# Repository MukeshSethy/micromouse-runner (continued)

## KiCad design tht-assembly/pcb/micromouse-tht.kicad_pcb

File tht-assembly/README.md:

# THT Assembly — the self-solderable micromouse carrier board (KiCad project)

This folder is the **executable KiCad project** for the all-THT edition
chartered in [`../tht-variant/`](../tht-variant/) (BOM research, architecture
decisions, ordering flow live there — read it first).

**Everything here is script-generated**, same discipline as the SMD board:

```
tht-assembly/
├── pcb/
│   ├── micromouse-tht.kicad_sch / .kicad_pcb   generated outputs
│   ├── netlist.net                             schematic's own export
│   ├── n20.pretty/                             optic footprints (shared)
│   └── tools/
│       ├── build_schematic_tht.py   FULL schematic (198 syms, ERC 0,
│       │                            RAIL-only — no wire doglegs possible)
│       ├── build_pcb_tht.py         outline + placement (measured-courtyard
│       │                            greedy packers; 0 overlaps) + planes
│       ├── route_tht.py             A* routing (power 0.8mm, signals 0.4mm)
│       └── verify_drc.py …          the SMD project's gate suite, path-adapted
└── images/                          renders
```

## Key physical decisions (why the board looks like this)
- **Sensor geometry copied verbatim** from the rev-7.2 SMD board (D1-D6,
  Q2-Q7 wall optics at 0°/45°/90°, LS1-LS8 line array) — it is the
  research-verified core of the robot and all three families were already THT.
- **DevKitC-1 lies across the rear** on two 1×22 sockets (rows y94.5/117.36,
  USB end to the right, kept clear). The SMD board's antenna notch is gone —
  the DevKit's antenna rides ~10 mm above the board.
- **The mux DIP is soldered flat under the DevKit deck** (no socket — 4.3 mm
  under an 8.5 mm deck). Everything else under the deck is bare board.
- **Bottom face carries the silent majority**: all 66 axial resistors,
  20 TO-92 transistors, the flyback diode and the piezo — all under the
  ~7 mm ride-height budget. Top face keeps everything you look at or touch:
  optics, LEDs, buttons, connectors, power bricks, sockets.
- **Motor bays own the waist** (x2.7-46.2 / x53.8-97.3, y76.9-91.1 top): the
  only top-face items there are the wall-LED row and motor connectors at its
  forward edge.

## Assembly / bring-up
Follow [`../tht-variant/ORDERING.md`](../tht-variant/ORDERING.md) (bare-PCB
fab + parts kit + three robu modules). Solder bottom-face resistors first
(board flat), then work upward by height. Firmware: the shared `fw/` tree —
GPIO numbers are IDENTICAL to the SMD board (same S3 silicon); flash through
the DevKit's own USB-C.

## Placement (pre-routing, for review)

> These are PLACEMENT renders (no traces yet) — routing + DRC follow. Wall
> sensors sit on the perimeter facing outward with clear IR paths; indicators
> are inboard behind them; all support parts + both RGB drivers + the buzzer
> are on the bottom face.

**Top** — sensors (perimeter), indicators (inboard), power block, DevKit +
TB6612 sockets, buttons, RGB LEDs:

**Bottom** — axial resistors, TO-92 transistors, buzzer, flyback diode:

## Status
See the milestone log in git (`THT assembly M1..`): schematic ERC 0 →
placement 0-overlap + optical-clear → routing → DRC gate → fab package.
**Current: placement complete & optically verified; routing in progress.**

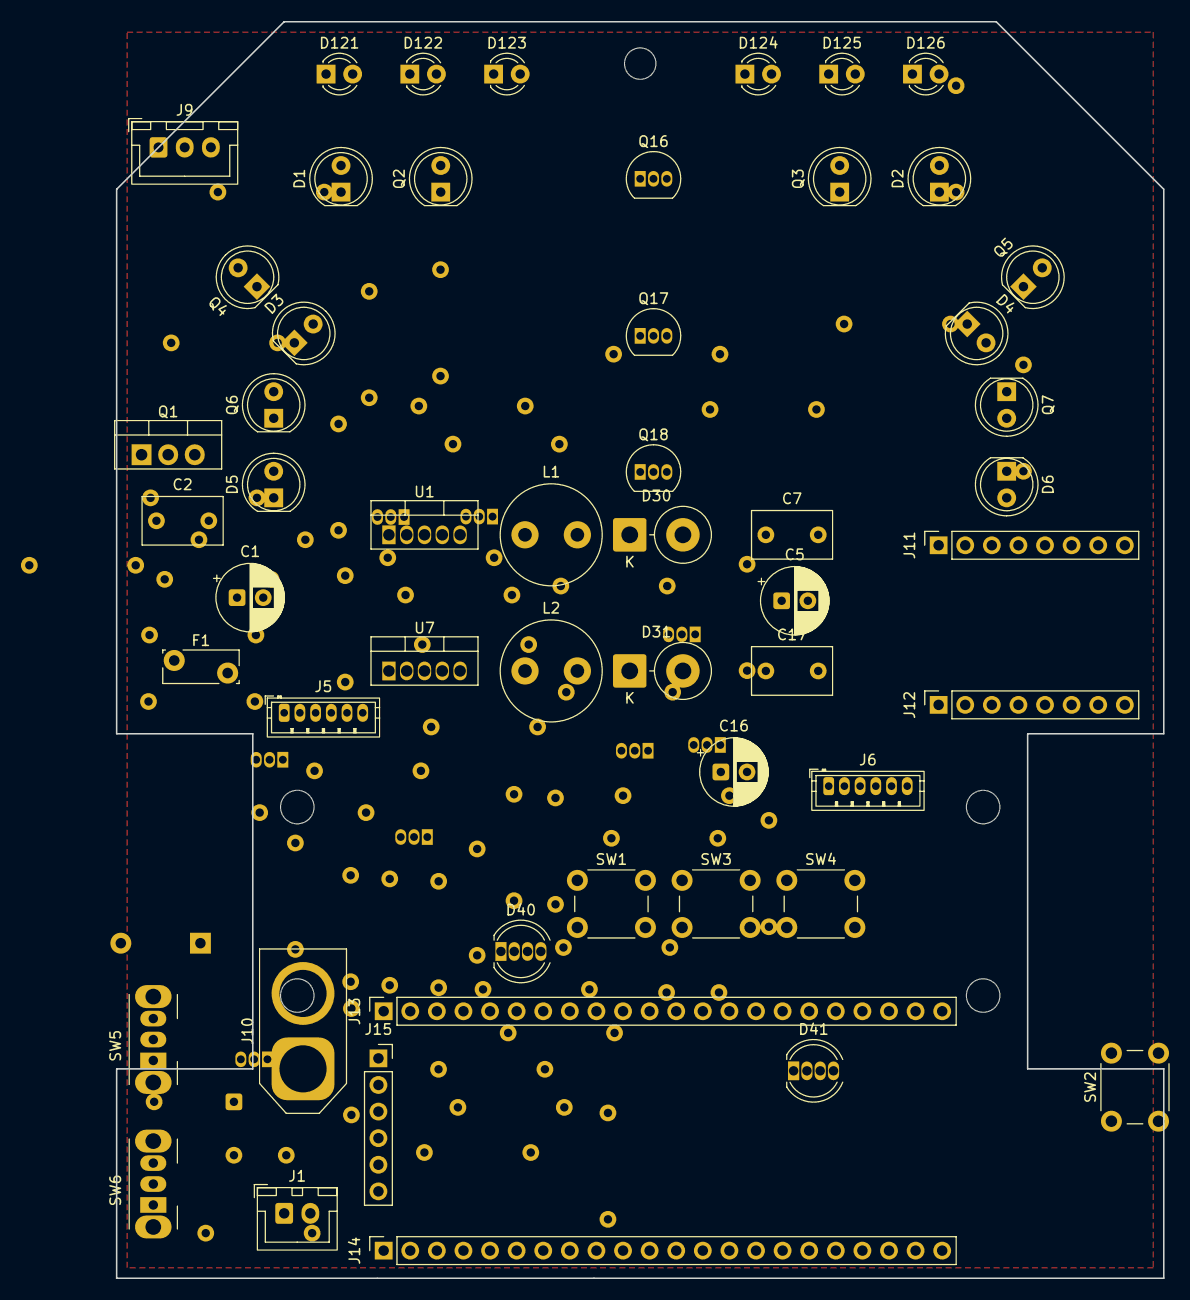
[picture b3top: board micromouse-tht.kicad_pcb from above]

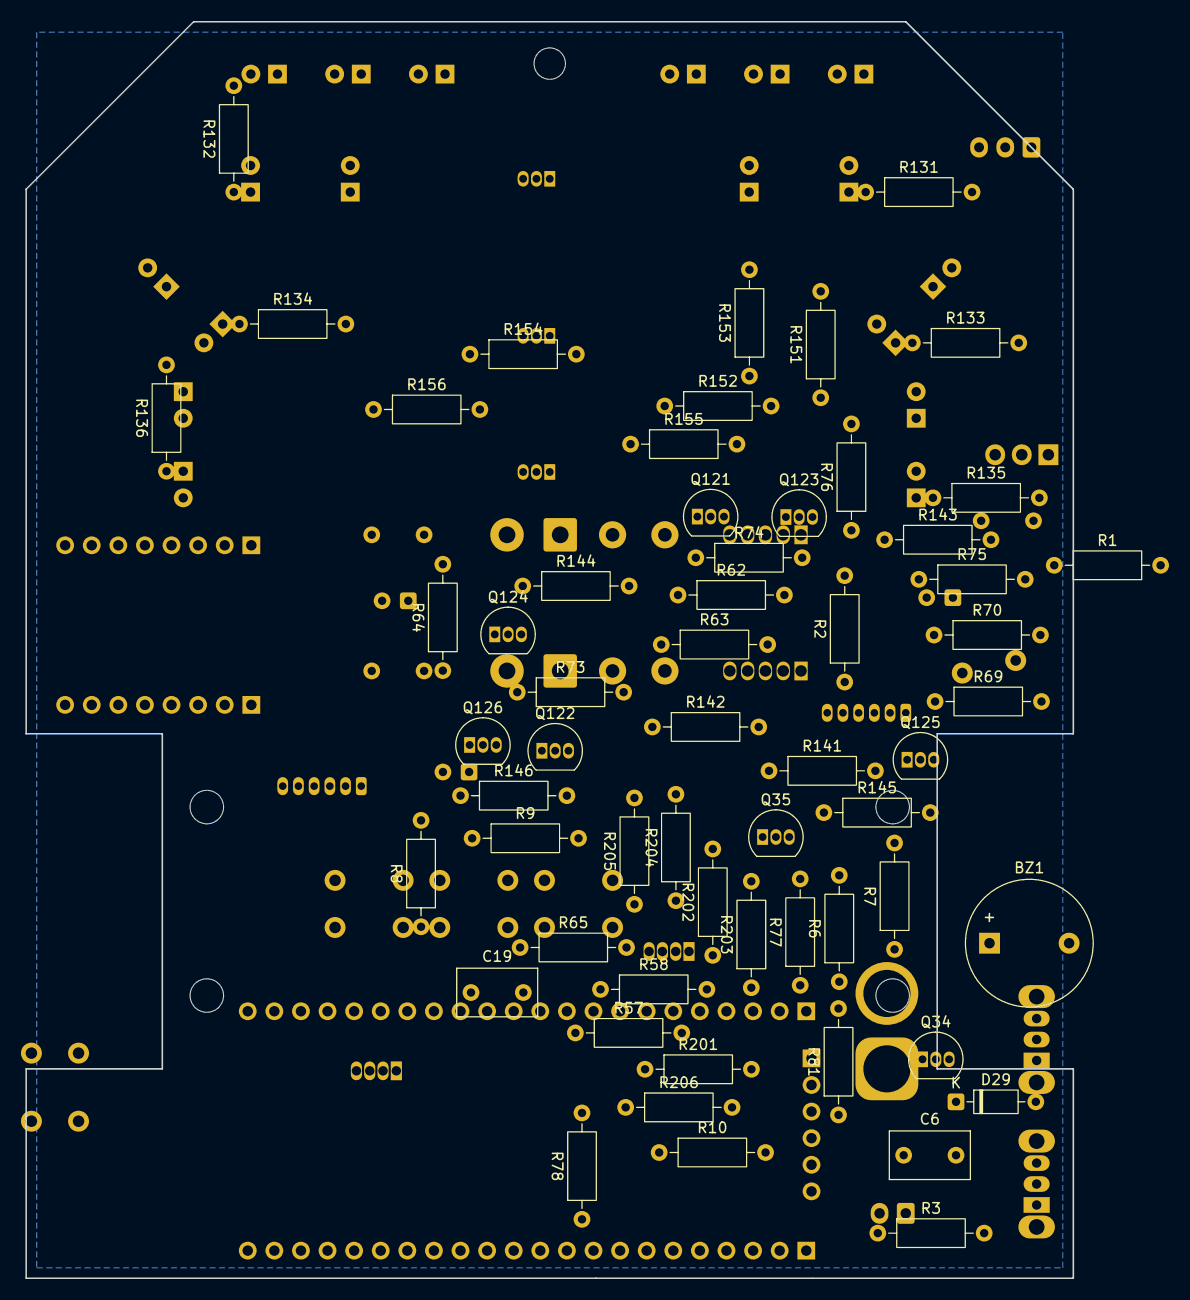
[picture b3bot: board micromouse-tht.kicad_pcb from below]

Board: 2 copper layers, 100.0 x 120.0 mm, 117 parts (59 on the bottom side), 82 nets, no tracks yet.

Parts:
BZ1: Buzzer_12x9.5RM7.6
C1, C5, C16: CP_Radial_D6.3mm_P2.50mm
C2, C6, C7, C17, C19: C_Disc_D7.5mm_W4.4mm_P5.00mm
D1, D2, D3, D4, D5, D6: LED_D5.0mm_IRGrey
D29: D_DO-35_SOD27_P7.62mm_Horizontal
D30, D31: D_DO-201AD_P5.08mm_Vertical_CathodeUp
D40, D41: LED_D5.0mm-4_RGB
D121, D122, D123, D124, D125, D126: LED_D3.0mm
F1: Fuse_Bourns_MF-RG300
H1, H2, H3, H4, H5: MountingHole_NPTH
J1: JST_XH_B2B-XH-A_1x02_P2.50mm_Vertical
J5, J6: JST_ZH_B6B-ZR_1x06_P1.50mm_Vertical
J9: JST_XH_B3B-XH-A_1x03_P2.50mm_Vertical
J10: AMASS_XT60-M_1x02_P7.20mm_Vertical
J11, J12: PinSocket_1x08_P2.54mm_Vertical
J13, J14: PinSocket_1x22_P2.54mm_Vertical
J15: PinSocket_1x06_P2.54mm_Vertical
L1, L2: L_Radial_D9.5mm_P5.00mm_Fastron_07HVP
Q1: TO-220-3_Vertical
Q2, Q3, Q4, Q5, Q6, Q7: LED_D5.0mm_IRBlack
Q16, Q17, Q18, Q34, Q35, Q121, Q122, Q123, Q124, Q125, Q126: TO-92_Inline
R1, R2, R3, R6, R7, R8, R9, R10, R57, R58, R62, R63, R64, R65, R69, R70, R73, R74, R75, R76, R77, R78, R81, R131, R132, R133, R134, R135, R136, R141, R142, R143, R144, R145, R146, R151, R152, R153, R154, R155, R156, R201, R202, R203, R204, R205, R206: R_Axial_DIN0207_L6.3mm_D2.5mm_P10.16mm_Horizontal
SW1, SW2, SW3, SW4: SW_PUSH_6mm
SW5, SW6: SW_Slide_SPDT_Angled_CK_OS102011MA1Q
U1, U7: TO-220-5_Vertical

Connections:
AIN1: J11.3, J13.15
AIN2: J11.2, J13.16
BATT_RAW: F1.1, J1.1, J9.3, J10.1
BAT_MID: J9.2, R75.1
BAT_MID_SENSE: C19.1, J13.12, R75.2, R76.1
BIN1: J11.5, J14.10
BIN2: J11.6, J14.15, R65.1
BUZZ_B: Q34.2, R81.2
BUZZ_CTRL: J13.14, R81.1
BUZZ_DRV: BZ1.2, D29.2, Q34.3
EMIT_DIAG_K: D3.1, D4.1, Q17.3
EMIT_FRONT_K: D1.1, D2.1, Q16.3
EMIT_SIDE_K: D5.1, D6.1, Q18.3
ENC1_A: J5.3, J14.17, R6.2
ENC1_B: J5.4, J14.16, R7.2
ENC2_A: J6.3, R8.2, R57.1
ENC2_A_S3: J14.3, R57.2
ENC2_B: J6.4, R9.2, R58.1
ENC2_B_S3: J14.2, R58.2
ESP_RST: J13.3, SW2.1
F1_OUT: F1.2, Q1.2
FB_6V: R73.2, R74.1, U7.4
GND: C1.2, C2.2, C5.2, C6.2, C7.2, C16.2, C17.2, C19.2, D30.2, D31.2, D40.2, D41.2, D121.1, D122.1, D123.1, D124.1, D125.1, D126.1, J1.2, J5.5, J6.5, J9.1, J10.2, J11.8, J12.3, J12.8, J13.22, J14.1, J14.21, J14.22, J15.2, Q2.2, Q3.2, Q4.2, Q5.2, Q6.2, Q7.2, Q16.1, Q17.1, Q18.1, Q34.1, R1.2, R3.2, R62.2, R63.2, R64.2, R65.2, R74.2, R76.2, SW1.2, SW2.2, SW3.2, SW4.2, SW5.3, SW6.3, U1.3, U7.3
IMU_INT: J14.11, J15.5
IMU_SCL: J14.18, J15.3, R78.2
IMU_SDA: J13.11, J15.4, R77.2
MOTA_N: J5.6, J12.5
MOTA_P: J5.1, J12.4
MOTB_N: J6.6, J12.6
MOTB_P: J6.1, J12.7
MOT_EN: Q35.3, R70.2, U7.5
MOT_EN_SW: Q35.1, SW6.1, SW6.2
unnamed: D1.2, R131.2
unnamed: D2.2, R132.2
unnamed: D3.2, R133.2
unnamed: D4.2, R134.2
unnamed: D5.2, R135.2
unnamed: D6.2, R136.2
PLUS3V3: BZ1.1, C5.1, C7.1, D29.1, J5.2, J6.2, J11.1, J11.4, J11.7, J12.2, J13.1, J13.2, J15.1, L1.2, Q35.2, Q121.3, Q122.3, Q123.3, Q124.3, Q125.3, Q126.3, R6.1, R7.1, R8.1, R9.1, R10.1, R77.1, R78.1, R131.1, R132.1, R133.1, R134.1, R135.1, R136.1, R141.1, R142.1, R143.1, R144.1, R145.1, R146.1, U1.4
PWR_EN: R69.2, SW5.1, SW5.2, U1.5
Q1_G: Q1.1, R1.1
RGB1_B: J13.19, R203.1
RGB1_BA: D40.4, R203.2
RGB1_G: J13.18, R202.1
RGB1_GA: D40.3, R202.2
RGB1_R: J13.17, R201.1
RGB1_RA: D40.1, R201.2
RGB2_B: J14.6, R206.1
RGB2_BA: D41.4, R206.2
RGB2_G: J13.21, R205.1
RGB2_GA: D41.3, R205.2
RGB2_R: J13.20, R204.1
RGB2_RA: D41.1, R204.2
SW_3V3: D30.1, L1.1, U1.2
SW_6V: D31.1, L2.1, U7.2
USER_BTN: J14.14, R10.2, SW1.1
USER_BTN2: J14.13, SW3.1
USER_BTN3: J14.12, SW4.1
VBAT_SENSE: C6.1, J13.7, R2.2, R3.1
VM_6V: C16.1, C17.1, J12.1, L2.2, R73.1
VM_BATT: C1.1, C2.1, Q1.3, R2.1, R69.1, R70.1, U1.1, U7.1
WALL1_SENSE: J14.4, Q2.1, Q121.2, R141.2
WALL2_SENSE: J14.5, Q3.1, Q122.2, R142.2
WALL3_SENSE: J13.13, Q4.1, Q123.2, R143.2
WALL4_SENSE: J13.4, Q5.1, Q124.2, R144.2
WALL5_SENSE: J13.5, Q6.1, Q125.2, R145.2
WALL6_SENSE: J13.6, Q7.1, Q126.2, R146.2
WALL_EMIT_DIAG: J13.9, Q17.2, R63.1
WALL_EMIT_FRONT: J13.8, Q16.2, R62.1
WALL_EMIT_SIDE: J13.10, Q18.2, R64.1
WIND1: Q121.1, R151.1
WIND2: Q122.1, R152.1
WIND3: Q123.1, R153.1
WIND4: Q124.1, R154.1
WIND5: Q125.1, R155.1
WIND6: Q126.1, R156.1
WLED1: D121.2, R151.2
WLED2: D122.2, R152.2
WLED3: D123.2, R153.2
WLED4: D124.2, R154.2
WLED5: D125.2, R155.2
WLED6: D126.2, R156.2

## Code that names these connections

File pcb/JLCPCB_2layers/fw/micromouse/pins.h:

// micromouse-pcb 2-LAYER JLCPCB edition -- GPIO map (single source of truth:
// pcb/JLCPCB_2layers/design/netlist.net; this header is GATED against that
// netlist by fw/check_pins.py, which fails the build chain if any assignment
// drifts from the board).
//
// Deltas vs the 4-layer rev-7.2 board:
//   * line-sensor array (TCRT5000 x8) + CD74HC4067 mux + per-line indicator
//     LEDs REMOVED -> no PIN_MUX_*, no PIN_EMIT_LINE, no mux channel map.
//   * battery / VBUS telemetry moved OFF the mux onto DIRECT ADC1 inputs
//     (IO7/IO8/IO9).
//   * AIN1 moved IO9 -> IO11 (IO9 now carries VBUS_SENSE).
//   * JTAG header (J8) removed -> IO39-42 are NC; flashing + debug are over
//     the ESP32-S3 native USB-Serial-JTAG only (IO19/IO20 via the USB-C port).
//   * added ESP-driven indicators: STATUS_LED (IO12) + WS2812B RGB (IO14).
// Two-switch scheme unchanged: SW5 = ALL logic rails, SW6 = 6V motor rail.
//
// All nets documented per-trace in the design's CONNECTIONS.md.
#pragma once

// ---- analog wall sensors (ADC1: GPIO1-10, usable with WiFi active) ----------
#define PIN_WALL1_SENSE   1   // net WALL1_SENSE  (FRONT-L PT334-6B, 47k pull-up)
#define PIN_WALL2_SENSE   2   // net WALL2_SENSE  (FRONT-R)
#define PIN_WALL3_SENSE   3   // net WALL3_SENSE  (DIAG-L, exact 45 deg)
#define PIN_WALL4_SENSE   4   // net WALL4_SENSE  (DIAG-R)
#define PIN_WALL5_SENSE   5   // net WALL5_SENSE  (SIDE-L, exact 90 deg)
#define PIN_WALL6_SENSE   6   // net WALL6_SENSE  (SIDE-R)

// ---- battery / bus telemetry (DIRECT ADC1 -- mux removed on 2-layer) --------
#define PIN_VBAT_SENSE    7   // net VBAT_SENSE     pack / (100k:39k)  = V*39/139
// IO8 free -- per-cell (BAT_MID_SENSE) removed with the balance connector
#define PIN_VBUS_SENSE    9   // net VBUS_SENSE     5V / (10k:15k)     = V*0.6

// ---- motor driver (TB6612FNG, IN/IN PWM mode) -------------------------------
// PWMA/PWMB/STBY are tied high ON THE BOARD. Drive per Toshiba's IN/IN table:
//   forward: IN1 = PWM, IN2 = 0   (coast in the off-phase)
//   reverse: IN1 = 0,   IN2 = PWM
//   brake:   IN1 = IN2 = 1
#define PIN_AIN1          11  // net AIN1 (LEDC)   [moved IO9 -> IO11; IO9 = VBUS_SENSE]
#define PIN_AIN2          10  // net AIN2 (LEDC)
#define PIN_BIN1          38  // net BIN1 (LEDC)
#define PIN_BIN2          45  // net BIN2 (LEDC; strap: 10k pulldown on board -> VDD_SPI 3.3V)

// ---- IR wall-emitter banks (BSS138 low-side gates, pulsed) ------------------
#define PIN_EMIT_FRONT    15  // net WALL_EMIT_FRONT
#define PIN_EMIT_DIAG     16  // net WALL_EMIT_DIAG
#define PIN_EMIT_SIDE     17  // net WALL_EMIT_SIDE

// ---- IMU (BNO055, I2C addr 0x28) --------------------------------------------
#define PIN_IMU_SDA       18  // net IMU_SDA (4.7k pull-up on board)
#define PIN_IMU_SCL       21  // net IMU_SCL (4.7k pull-up on board)
#define PIN_IMU_INT       37  // net IMU_INT (BNO055 INT out)
#define IMU_I2C_ADDR      0x28   // internal osc (no external crystal)

// ---- encoders (PCNT hardware quadrature) ------------------------------------
#define PIN_ENC1_A        47  // net ENC1_A (motor A, 10k pull-up on board)
#define PIN_ENC1_B        48  // net ENC1_B
#define PIN_ENC2_A        44  // net ENC2_A_S3 side (1k UART0 guard on board)
#define PIN_ENC2_B        43  // net ENC2_B_S3 side (1k UART0 guard on board)

// ---- ESP-driven indicators (2-layer additions) -----------------------------
#define PIN_STATUS_LED    12  // net STATUS_LED (1k -> D31 SMD status LED; dev-board heartbeat)
#define PIN_RGB_DATA      14  // net RGB_DATA   (D32 WS2812B addressable RGB; 3.3V data OK)
// D30 power LED is hardwired to +3V3 and D33 motor LED to VM_6V -- no GPIO.

// ---- user I/O ---------------------------------------------------------------
#define PIN_BTN_A         0   // net USER_BTN  on SW1 -> GND, 10k pull-up (also BOOT strap)
#define PIN_BTN_B         35  // net USER_BTN2 on SW3 -> GND, use INPUT_PULLUP (internal)
#define PIN_BTN_C         36  // net USER_BTN3 on SW4 -> GND, use INPUT_PULLUP (internal)
#define PIN_BUZZER        46  // net BUZZ_CTRL: 220R -> MMBT2222A base -> CMT-8504 magnetic
                              // buzzer (4kHz rated). Strap-safe: the base load only ever
                              // pulls IO46 LOW (its boot default); LEDC ~4kHz square = beep.

// ---- battery policy (2S) ----------------------------------------------------
#define VBAT_DIVIDER      (139.0f / 39.0f)   // pack divider inverse (100k:39k)
#define VBUS_DIVIDER      (25.0f / 15.0f)    // VBUS divider inverse (10k:15k)
#define PACK_CUTOFF_V     6.6f               // 2S pack floor (3.3V/cell avg); PACK-LEVEL only

// USB D-/D+ are the S3 native pins IO19/IO20 (flashing + CDC console).
// 2-layer: NO JTAG header -- IO39-42 are NC; debug is over native USB only.

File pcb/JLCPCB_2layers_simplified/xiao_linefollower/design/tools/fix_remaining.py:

"""Targeted retry for the specific nets route_all.py could not close after 4
escalating rounds + 5 reorder retries (52/72 nets succeeded there). Loads the
board AS-IS (route_all.py's own save, ~4100 tracks/242 vias already placed --
never re-runs build_pcb.py, which would discard that work). Uses much larger
max_expansions/smaller grid on just the known-stuck nets, since "far apart"
is a search-budget problem, not necessarily an impossibility. GND gets a
dedicated zone-fill + largest-fragment-bridge pass (it's poured, not routed
point-to-point).
"""
import sys, os, math
sys.path.insert(0, os.path.dirname(os.path.abspath(__file__)))
import pcbnew
from gen_pcb import PcbGen
from board_geom import BOARD_OUTLINE, WHEEL_NOTCHES, MOUNT_HOLES

BASE = os.path.normpath(os.path.join(os.path.dirname(os.path.abspath(__file__)), ".."))
BOARD = os.path.join(BASE, "micromouse-pcb-simplified.kicad_pcb")
NETLIST = os.path.join(BASE, "netlist.net")

STUCK_NETS = ['PWRLED_A', 'WALL_DL_SENSE', 'Net-(D46-K)', 'VM_6V', 'GND', 'Net-(D42-K)',
              'Net-(Q46-Pin_1)', 'BIN1', 'WALL_FL_SENSE', 'Net-(Q45-Pin_1)', 'WALL_EMIT_SIDE',
              'Net-(D45-K)', 'Net-(SW7-B)', 'WALL_EMIT_FRONT', 'Net-(U4-REFin{slash}REFout)',
              'Net-(D44-K)', 'Net-(Q44-Pin_1)', 'Net-(D43-K)', 'Net-(D2-A)', 'WALL_DR_SENSE']


def load():
    g = PcbGen(NETLIST)
    g.board = pcbnew.LoadBoard(BOARD)
    g.setup_design_rules()
    # This script deliberately routes a handful of stuck nets at 0.15mm
    # width / 0.127mm clearance -- both still within JLCPCB's documented
    # real fab minimum (0.127mm track/clearance), so the board-wide minimum
    # rules must be relaxed to match or these tracks would be DRC
    # violations despite routing successfully. Everything else on the board
    # stays at the wider 0.2/0.3mm the rest of the design already uses.
    bds = g.board.GetDesignSettings()
    bds.m_TrackMinWidth = pcbnew.FromMM(0.127)
    try:
        bds.m_NetSettings.GetDefaultNetclass().SetClearance(pcbnew.FromMM(0.127))
    except Exception:
        pass
    g.LAYERS = [pcbnew.F_Cu, pcbnew.B_Cu]
    g._placed = {fp.GetReference(): fp for fp in g.board.GetFootprints()}
    g._nets = {}
    for code, ni in g.board.GetNetsByNetcode().items():
        if ni.GetNetname():
            g._nets[ni.GetNetname()] = ni
    g._outline_pts = list(BOARD_OUTLINE)
    g._extra_keepouts = []
    for (sx1, sy1, sx2, sy2) in WHEEL_NOTCHES:
        g._extra_keepouts.append((sx1 - 0.6, sy1 - 0.6, sx2 + 0.6, sy2 + 0.6))
    for (hx, hy, hr) in MOUNT_HOLES:
        m = hr + 0.75
        g._extra_keepouts.append((hx - m, hy - m, hx + m, hy + m))
    g._pads_geo_cache = None
    g._track_segs, g._vias = [], []
    for t in g.board.GetTracks():
        net = t.GetNet().GetNetname()
        if t.GetClass() == "PCB_VIA":
            p = t.GetPosition()
            g._vias.append((pcbnew.ToMM(p.x), pcbnew.ToMM(p.y), net,
                            pcbnew.ToMM(t.GetWidth(pcbnew.F_Cu)) / 2))
        elif t.GetClass() == "PCB_TRACK":
            a, b = t.GetStart(), t.GetEnd()
            g._track_segs.append(((pcbnew.ToMM(a.x), pcbnew.ToMM(a.y)),
                                  (pcbnew.ToMM(b.x), pcbnew.ToMM(b.y)), net,
                                  pcbnew.ToMM(t.GetWidth()) / 2, t.GetLayer()))
    g._unrouted = []
    return g


def bridge_gnd_fragments(g):
    """Same-net via bridge between the largest GND fill fragment and every
    smaller one, on each copper layer -- standard fix for a poured net that
    DRC/route_net reports as one unconnected item (zone fragments = islands
    the router can't join by definition, since it isn't a 2-pad route)."""
    n_bridged = 0
    for layer in (pcbnew.F_Cu, pcbnew.B_Cu):
        zone = None
        for z in g.board.Zones():
            if z.GetNetname() == "GND" and z.GetLayer() == layer:
                zone = z
        if zone is None:
            continue
        poly = zone.GetFilledPolysList(layer)
        if poly.OutlineCount() <= 1:
            continue
        areas = [(abs(poly.Outline(i).Area()), i) for i in range(poly.OutlineCount())]
        main = max(areas)[1]
        main_chain = poly.Outline(main)
        for (_, fi) in areas:
            if fi == main:
                continue
            chain = poly.Outline(fi)
            bb = chain.BBox()
            cx = (pcbnew.ToMM(bb.GetLeft()) + pcbnew.ToMM(bb.GetRight())) / 2
            cy = (pcbnew.ToMM(bb.GetTop()) + pcbnew.ToMM(bb.GetBottom())) / 2
            # nearest point on the MAIN outline to this fragment's centroid
            best = None
            for j in range(main_chain.PointCount()):
                pt = main_chain.CPoint(j)
                mx, my = pcbnew.ToMM(pt.x), pcbnew.ToMM(pt.y)
                d = math.hypot(mx - cx, my - cy)
                if best is None or d < best[0]:
                    best = (d, (mx, my))
            if best is None:
                continue
            target = best[1]
            placed_frag = placed_main = None
            for ddx in (0.0, 0.5, -0.5, 1.0, -1.0):
                for ddy in (0.0, 0.5, -0.5, 1.0, -1.0):
                    v = (round(cx + ddx, 3), round(cy + ddy, 3))
                    pv = pcbnew.VECTOR2I(pcbnew.FromMM(v[0]), pcbnew.FromMM(v[1]))
                    if chain.PointInside(pv, 0, True) and g._verify_geo([], [v], "GND", 0.125) is None:
                        placed_frag = v
                        break
                if placed_frag:
                    break
            if placed_frag and g.retry_edge("GND", placed_frag, target, width_mm=0.3,
                                             clearance_mm=0.15, grid_mm=0.15, max_expansions=500000):
                print(f"  GND fragment bridge ({pcbnew.LayerName(layer)}) {placed_frag} -> {target}")
                n_bridged += 1
    return n_bridged


def main():
    g = load()
    remaining = []
    for name in STUCK_NETS:
        if name == "GND":
            continue
        ok = False
        # These parameter tiers are DELIBERATELY at/near JLCPCB's absolute
        # fab minimum (0.127mm track/clearance) -- route_all.py already
        # exhausted every tier down to (0.2, 0.13) on these specific nets
        # with "no path found"/"too close to X" (an exhaustive search
        # result, not a budget cutoff -- more max_expansions would not have
        # helped), so repeating similar values is pointless. Going tighter
        # is the only lever left short of moving placement.
        for (w, clr, grid, maxexp) in (
            (0.15, 0.127, 0.1, 600000),
            (0.15, 0.127, 0.08, 900000),
        ):
            g._unrouted = []
            ok = g.route_net(name, width_mm=w, clearance_mm=clr, grid_mm=grid, max_expansions=maxexp)
            if ok:
                print(f"OK {name} width={w} clr={clr} grid={grid}", flush=True)
                break
            else:
                print(f"  {name} attempt width={w} clr={clr} grid={grid}: FAILED "
                      f"({g._unrouted[-1][3] if g._unrouted else '?'})", flush=True)
        if not ok:
            remaining.append(name)
        else:
            pcbnew.SaveBoard(BOARD, g.board)   # incremental save after every success

    print("fill_zones:", g.fill_zones(), flush=True)
    n = bridge_gnd_fragments(g)
    print(f"GND fragments bridged: {n}", flush=True)
    print("fill_zones (post-bridge):", g.fill_zones(), flush=True)

    pcbnew.SaveBoard(BOARD, g.board)
    print("saved", BOARD, flush=True)
    print("STILL UNROUTED (non-GND):", remaining, flush=True)


if __name__ == "__main__":
    main()
